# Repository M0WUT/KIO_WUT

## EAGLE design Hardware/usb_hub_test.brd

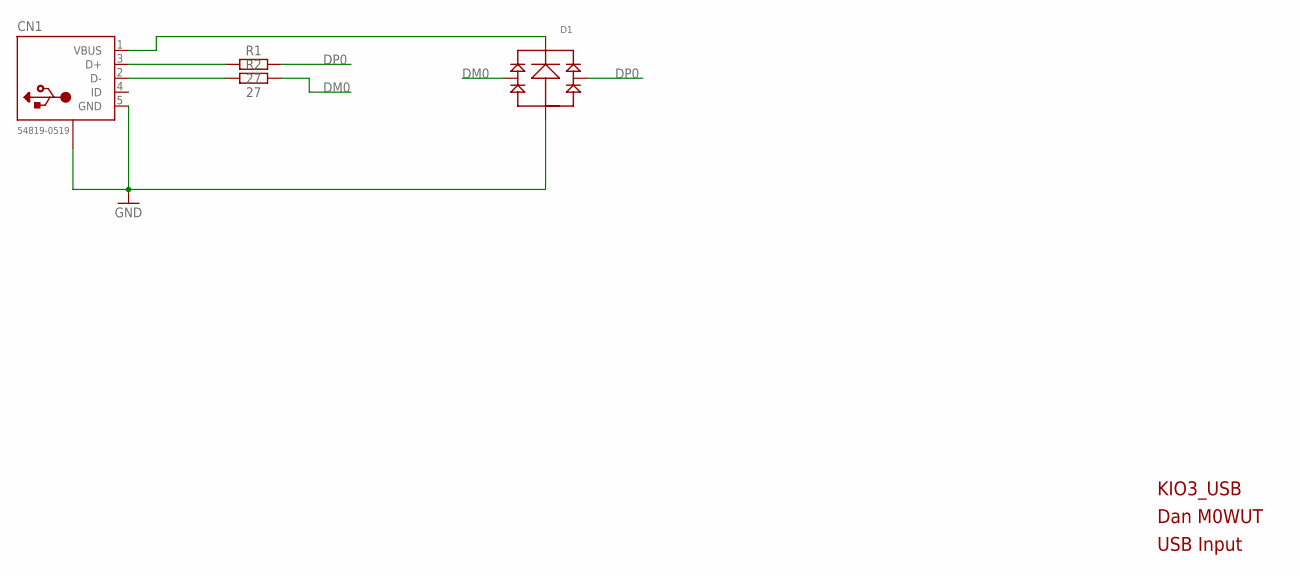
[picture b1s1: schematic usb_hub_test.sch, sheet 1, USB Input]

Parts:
CN1: 54819-0519; CONN_AMP_MUSB_K152
D1: D_ST_USBULC6; UQFN6
R1, R2: 27; R0402

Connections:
D+_P: CN1.3 (D+), R1.1
DM0: D1.1 (LEFT), D1.6 (LEFT), R2.2; also elsewhere on the board
DP0: D1.3 (RIGHT), D1.4 (RIGHT), R1.2; also elsewhere on the board
GND: CN1.5 (GND), CN1.GND1 (SHIELD), CN1.GND2 (SHIELD), D1.2 (GND); also elsewhere on the board
unnamed: CN1.2 (D-), R2.1
VBUS: CN1.1 (VBUS), D1.5 (V+)

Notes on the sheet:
KIO3_USB
Dan M0WUT
USB Input

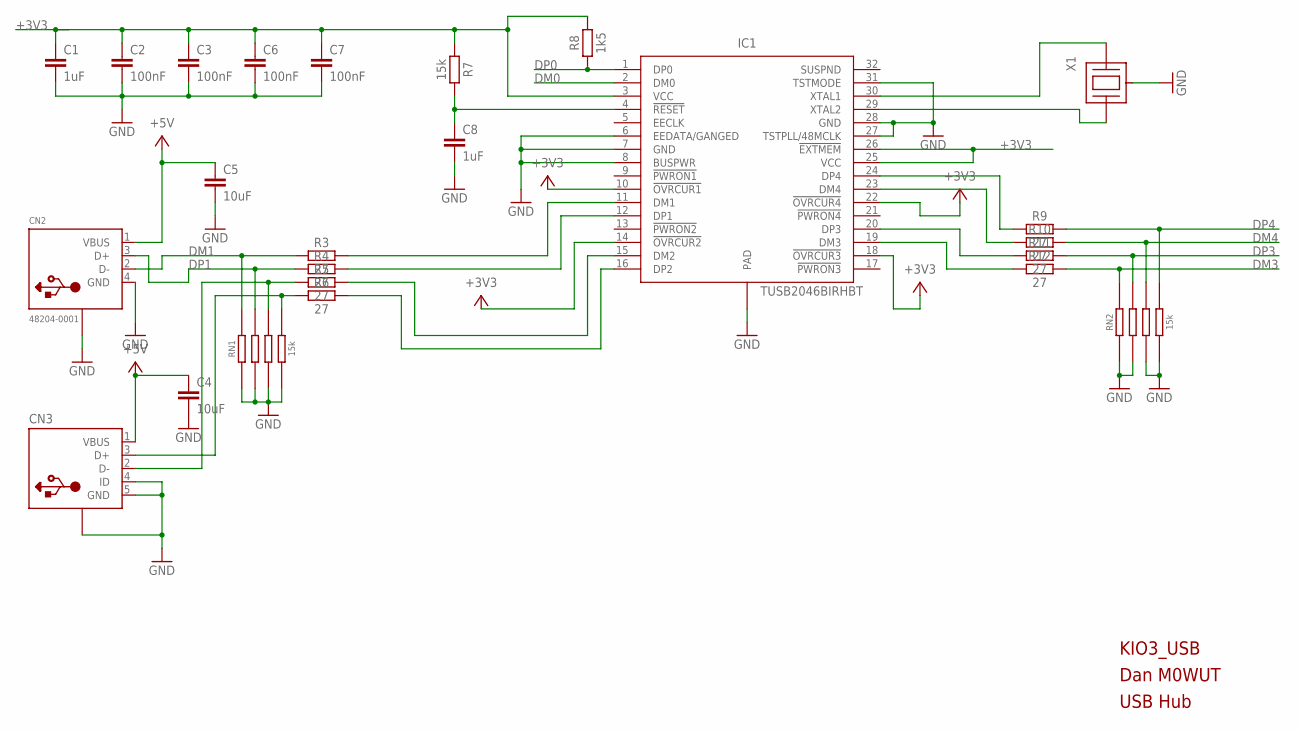
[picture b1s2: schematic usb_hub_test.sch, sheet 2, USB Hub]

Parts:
C1, C8: 1uF; C0402
C2, C3, C6, C7: 100nF; C0402
C4, C5: 10uF; C0805
CN2: 48204-0001; CONN_USB_MOLEX_RA
CN3: USBWURTH; USB_MICROB_WURTH
IC1: TUSB2046BIRHBT; RHB_S-PQFP-N32
R3, R4, R5, R6, R9, R10, R11, R12: 27; R0402
R7: 15k; R0402
R8: 1k5; R0402
RN1, RN2: 15k; R_BOURNS_CAY16-J4
X1: XTAL_MURATA_3-PIN-RES

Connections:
+3V3: C1.1, C2.1, C3.1, C6.1, C7.1, IC1.3 (VCC), IC1.10 (!OVRCUR1), IC1.14 (!OVRCUR2), IC1.18 (!OVRCUR3), IC1.22 (!OVRCUR4), IC1.25 (VCC), IC1.26 (!EXTMEM), R7.1, R8.2; also elsewhere on the board
+5V: C4.1, C5.1, CN2.1 (VBUS), CN3.1 (VBUS); also elsewhere on the board
DM0: IC1.2 (DM0); also elsewhere on the board
DM1: CN2.2 (D-), R3.1, RN1.1A
DM2: CN3.2 (D-), R5.1, RN1.3A
DM3: R12.2, RN2.1A; also elsewhere on the board
DM4: R10.2, RN2.3A; also elsewhere on the board
DP0: IC1.1 (DP0), R8.1; also elsewhere on the board
DP1: CN2.3 (D+), R4.1, RN1.2A
DP2: CN3.3 (D+), R6.1, RN1.4A
DP3: R11.2, RN2.2A; also elsewhere on the board
DP4: R9.2, RN2.4A; also elsewhere on the board
GND: C1.2, C2.2, C3.2, C4.2, C5.2, C6.2, C7.2, C8.2, CN2.4 (GND), CN2.P$2 (SHIELD), CN2.P$3 (SHIELD), CN2.P$4 (SHIELD), CN2.P$5 (SHIELD), CN3.4 (ID), CN3.5 (GND), CN3.GND1 (SHIELD), CN3.GND2 (SHIELD), CN3.GND3 (SHIELD), CN3.GND4 (SHIELD), IC1.6 (EEDATA/GANGED), IC1.7 (GND), IC1.8 (BUSPWR), IC1.27 (TSTPLL/48MCLK), IC1.28 (GND), IC1.31 (TSTMODE), IC1.EXP (PAD), RN1.1, RN1.2, RN1.3, RN1.4, RN2.1, RN2.2, RN2.3, RN2.4, X1.GND (CAN); also elsewhere on the board
unnamed: IC1.23 (DM4), R10.1
unnamed: IC1.24 (DP4), R9.1
unnamed: IC1.30 (XTAL1), X1.1 (XTAL1)
unnamed: C8.1, IC1.4 (!RESET), R7.2
unnamed: IC1.29 (XTAL2), X1.2 (XTAL2)
unnamed: IC1.15 (DM2), R5.2
unnamed: IC1.11 (DM1), R3.2
unnamed: IC1.12 (DP1), R4.2
unnamed: IC1.16 (DP2), R6.2
unnamed: IC1.20 (DP3), R11.1
unnamed: IC1.19 (DM3), R12.1

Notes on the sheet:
KIO3_USB
Dan M0WUT
USB Hub

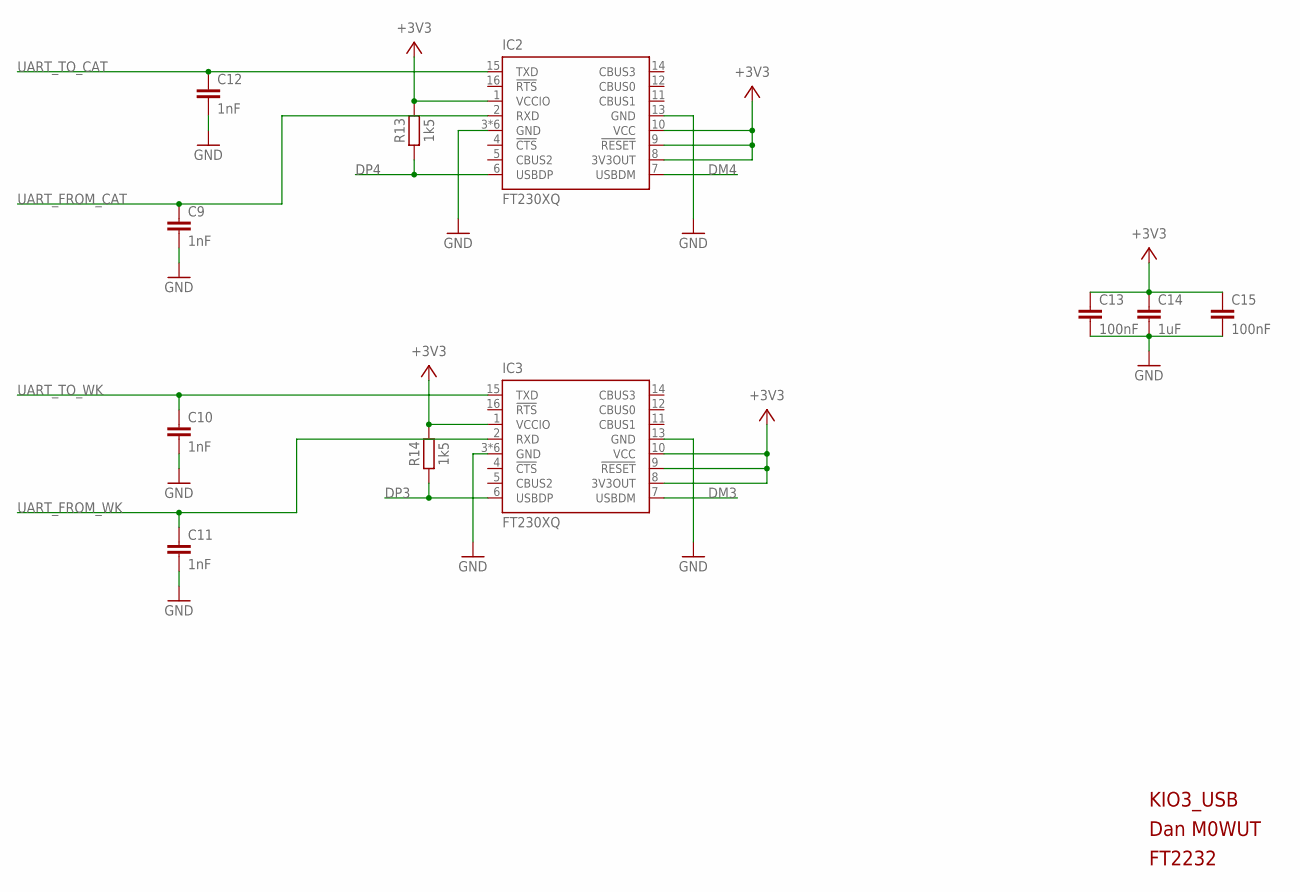
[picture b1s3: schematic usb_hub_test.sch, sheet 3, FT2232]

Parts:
C9, C10, C11, C12: 1nF; C0402
C13, C15: 100nF; C0402
C14: 1uF; C0402
IC2, IC3: FT230XQ; QFN16
R13, R14: 1k5; R0402

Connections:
+3V3: C13.1, C14.1, C15.1, IC2.1 (VCCIO), IC2.8 (3V3OUT), IC2.9 (!RESET), IC2.10 (VCC), IC3.1 (VCCIO), IC3.8 (3V3OUT), IC3.9 (!RESET), IC3.10 (VCC), R13.2, R14.2; also elsewhere on the board
DM3: IC3.7 (USBDM); also elsewhere on the board
DM4: IC2.7 (USBDM); also elsewhere on the board
DP3: IC3.6 (USBDP), R14.1; also elsewhere on the board
DP4: IC2.6 (USBDP), R13.1; also elsewhere on the board
GND: C9.2, C10.2, C11.2, C12.2, C13.2, C14.2, C15.2, IC2.3 (GND), IC2.13 (GND), IC2.P$1 (GND), IC2.P$2 (GND), IC2.P$3 (GND), IC2.P$4 (GND), IC2.TAB (GND), IC3.3 (GND), IC3.13 (GND), IC3.P$1 (GND), IC3.P$2 (GND), IC3.P$3 (GND), IC3.P$4 (GND), IC3.TAB (GND); also elsewhere on the board
UART_FROM_CAT: C9.1, IC2.2 (RXD); also elsewhere on the board
UART_FROM_WK: C11.1, IC3.2 (RXD); also elsewhere on the board
UART_TO_CAT: C12.1, IC2.15 (TXD); also elsewhere on the board
UART_TO_WK: C10.1, IC3.15 (TXD); also elsewhere on the board

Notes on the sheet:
KIO3_USB
Dan M0WUT
FT2232

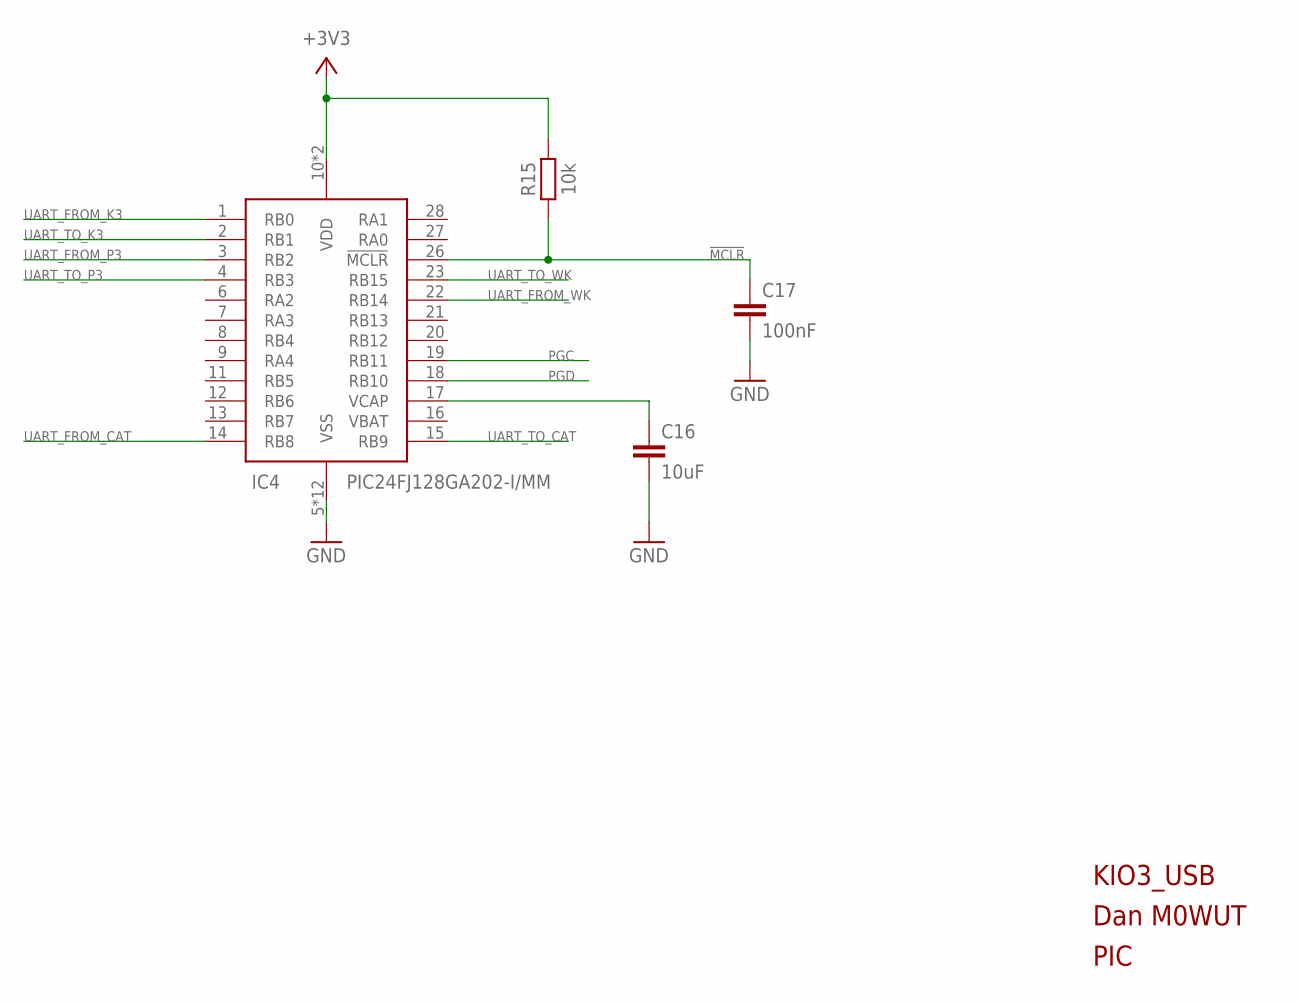
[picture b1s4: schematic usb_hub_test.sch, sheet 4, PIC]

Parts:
C16: 10uF; C0805
C17: 100nF; C0402
IC4: PIC24FJ128GA202-I/MM; QFN28-ML_6X6MM
R15: 10k; R0402

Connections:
!MCLR: C17.1, IC4.26 (!MCLR), R15.1
+3V3: IC4.10 (VDD), IC4.25 (VDD), R15.2; also elsewhere on the board
GND: C16.2, C17.2, IC4.5 (VSS), IC4.24 (VSS), IC4.EXP (VSS), IC4.P$1 (VSS), IC4.P$2 (VSS), IC4.P$3 (VSS), IC4.P$4 (VSS), IC4.P$5 (VSS), IC4.P$6 (VSS), IC4.P$7 (VSS), IC4.P$9 (VSS), IC4.P$10 (VSS); also elsewhere on the board
unnamed: C16.1, IC4.17 (VCAP)
PGC: IC4.19 (RB11)
PGD: IC4.18 (RB10)
UART_FROM_CAT: IC4.14 (RB8); also elsewhere on the board
UART_FROM_K3: IC4.1 (RB0); also elsewhere on the board
UART_FROM_P3: IC4.3 (RB2); also elsewhere on the board
UART_FROM_WK: IC4.22 (RB14); also elsewhere on the board
UART_TO_CAT: IC4.15 (RB9); also elsewhere on the board
UART_TO_K3: IC4.2 (RB1); also elsewhere on the board
UART_TO_P3: IC4.4 (RB3); also elsewhere on the board
UART_TO_WK: IC4.23 (RB15); also elsewhere on the board

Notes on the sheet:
KIO3_USB
Dan M0WUT
PIC

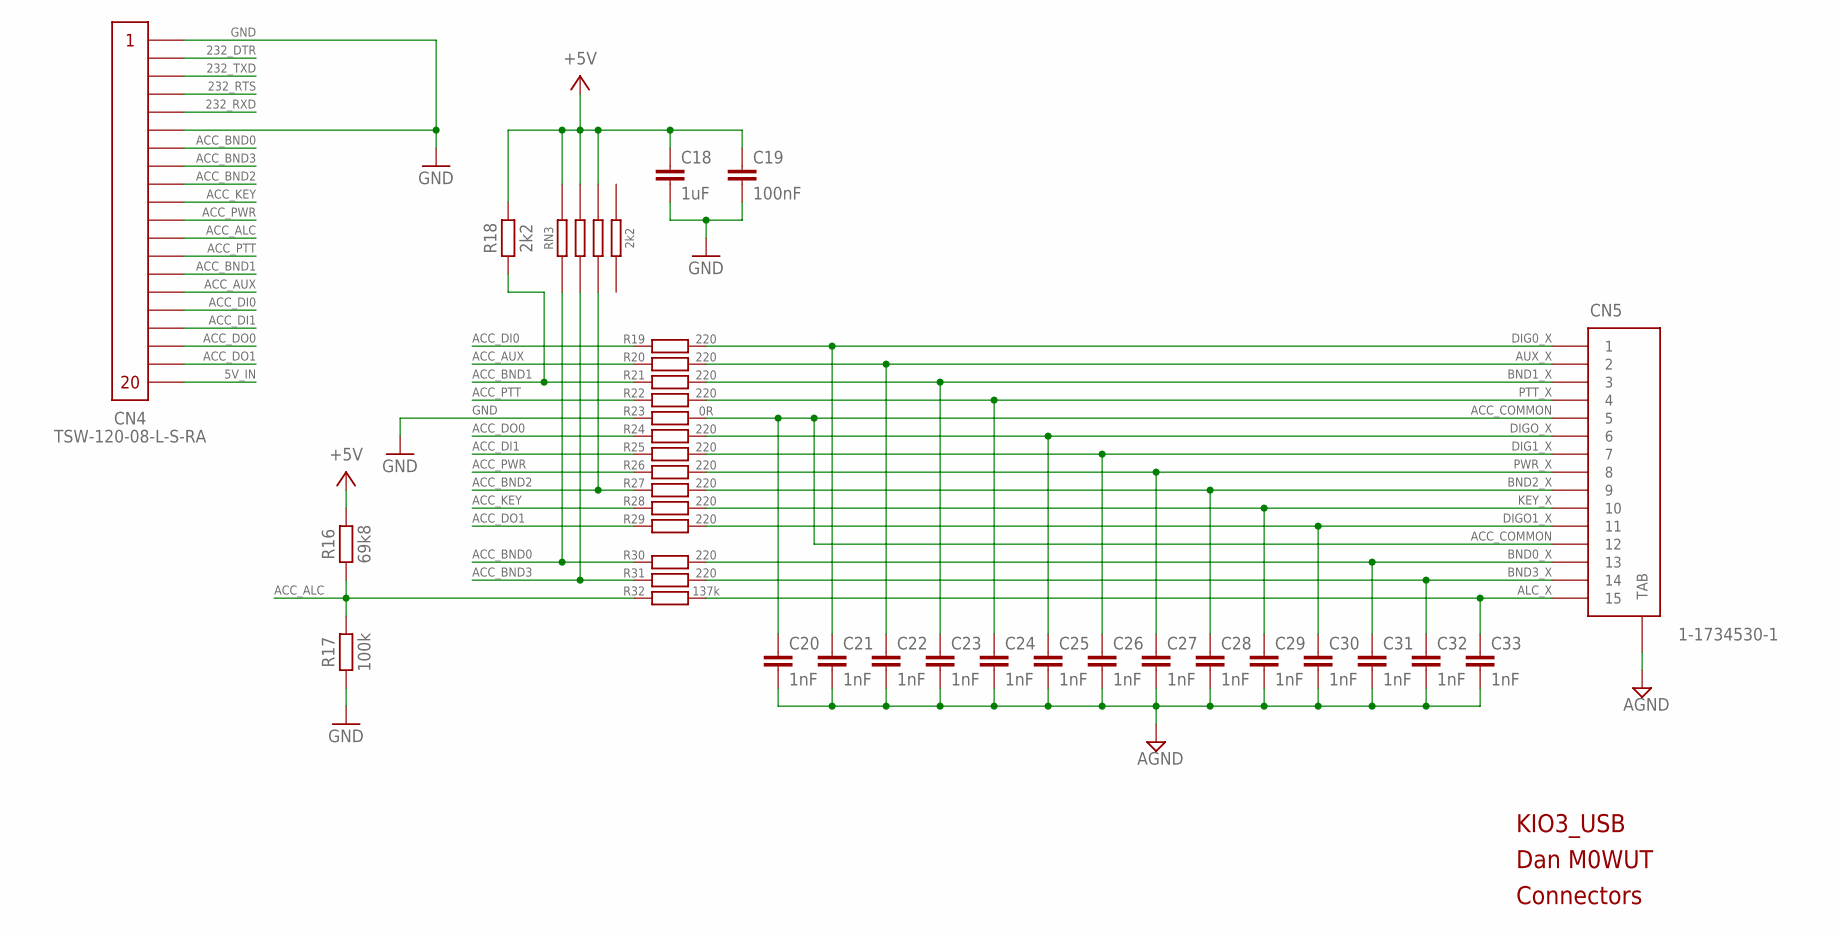
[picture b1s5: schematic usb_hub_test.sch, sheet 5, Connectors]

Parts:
C18: 1uF; C0402
C19: 100nF; C0402
C20, C21, C22, C23, C24, C25, C26, C27, C28, C29, C30, C31, C32, C33: 1nF; C0402
CN4: TSW-120-08-L-S-RA; CONN_0.1_1X20
CN5: 1-1734530-1; CONN_TE_DE-HD15
R16: 69k8; R0402
R17: 100k; R0402
R18: 2k2; R0402
R19, R20, R21, R22, R24, R25, R26, R27, R28, R29, R30, R31: 220; R0402
R23: 0R; R0402
R32: 137k; R0402
RN3: 2k2; R_BOURNS_CAY16-J4

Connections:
5V_IN: CN4.P$20; also elsewhere on the board
232_DTR: CN4.P$2
232_RTS: CN4.P$4
232_RXD: CN4.P$5; also elsewhere on the board
232_TXD: CN4.P$3; also elsewhere on the board
+5V: C18.1, C19.1, R16.2, R18.2, RN3.1, RN3.2, RN3.3; also elsewhere on the board
ACC_ALC: CN4.P$12, R16.1, R17.2, R32.1
ACC_AUX: CN4.P$15, R20.1
ACC_BND0: CN4.P$7, R30.1, RN3.1A
ACC_BND1: CN4.P$14, R18.1, R21.1
ACC_BND2: CN4.P$9, R27.1, RN3.3A
ACC_BND3: CN4.P$8, R31.1, RN3.2A
ACC_COMMON: C20.1, CN5.5, CN5.12, R23.2
ACC_DI0: CN4.P$16, R19.1
ACC_DI1: CN4.P$17, R25.1
ACC_DO0: CN4.P$18, R24.1
ACC_DO1: CN4.P$19, R29.1
ACC_KEY: CN4.P$10, R28.1
ACC_PTT: CN4.P$13, R22.1
ACC_PWR: CN4.P$11, R26.1
AGND: C20.2, C21.2, C22.2, C23.2, C24.2, C25.2, C26.2, C27.2, C28.2, C29.2, C30.2, C31.2, C32.2, C33.2, CN5.16 (TAB), CN5.17 (TAB); also elsewhere on the board
ALC_X: C33.1, CN5.15, R32.2
AUX_X: C22.1, CN5.2, R20.2
BND0_X: C31.1, CN5.13, R30.2
BND1_X: C23.1, CN5.3, R21.2
BND2_X: C28.1, CN5.9, R27.2
BND3_X: C32.1, CN5.14, R31.2
DIG0_X: C21.1, CN5.1, R19.2
DIG1_X: C26.1, CN5.7, R25.2
DIGO1_X: C30.1, CN5.11, R29.2
DIGO_X: C25.1, CN5.6, R24.2
GND: C18.2, C19.2, CN4.P$1, CN4.P$6, R17.1, R23.1; also elsewhere on the board
KEY_X: C29.1, CN5.10, R28.2
PTT_X: C24.1, CN5.4, R22.2
PWR_X: C27.1, CN5.8, R26.2

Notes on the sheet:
KIO3_USB
Dan M0WUT
Connectors

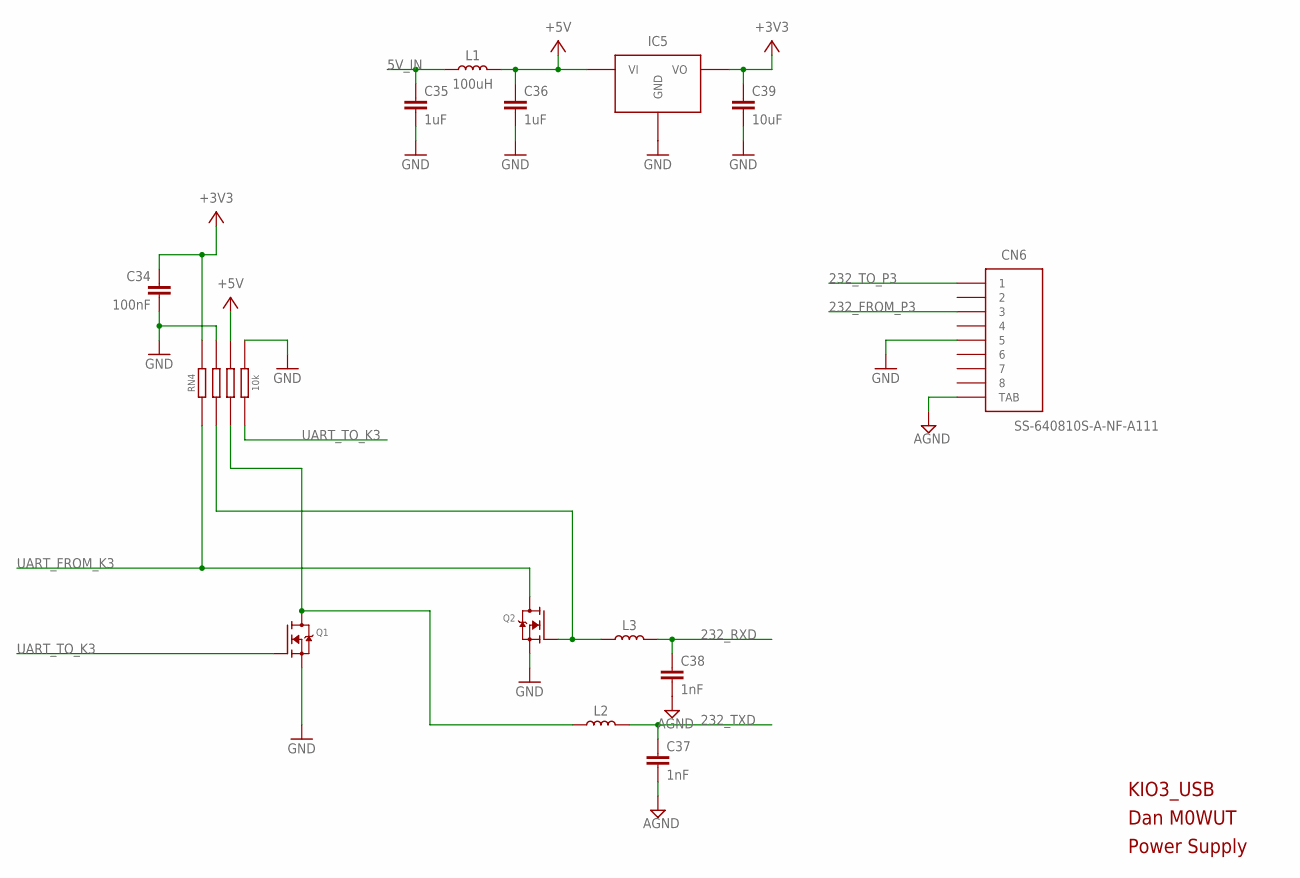
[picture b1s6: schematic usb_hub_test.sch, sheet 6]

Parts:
C34: 100nF; C0402
C35, C36: 1uF; C0402
C37, C38: 1nF; C0402
C39: 10uF; C0805
CN6: SS-640810S-A-NF-A111; CONN_STEWART_RJ45_1
IC5: MCP1700; SOT23
L1: 100uH; R0805
L2, L3: INDUCTOR; R0805
Q1, Q2: MOSFET-NREFLOW; SOT23
RN4: 10k; R_BOURNS_CAY16-J4

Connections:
5V_IN: C35.1, L1.1; also elsewhere on the board
232_FROM_P3: CN6.3; also elsewhere on the board
232_RXD: C38.1, L3.2; also elsewhere on the board
232_TO_P3: CN6.1; also elsewhere on the board
232_TXD: C37.1, L2.2; also elsewhere on the board
+3V3: C34.1, C39.1, IC5.BOTTOM_RIGHT (VO), RN4.1A; also elsewhere on the board
+5V: C36.1, IC5.TOP (VI), L1.2, RN4.3A; also elsewhere on the board
AGND: C37.2, C38.2, CN6.TAB, CN6.TAB1 (TAB); also elsewhere on the board
ASDF: L2.1, Q1.3 (D), RN4.3
GND: C34.2, C35.2, C36.2, C39.2, CN6.5, IC5.BOTTOM_LEFT (GND), Q1.2 (S), Q2.2 (S), RN4.2A, RN4.4A; also elsewhere on the board
SADF: L3.1, Q2.1 (G), RN4.2
UART_FROM_K3: Q2.3 (D), RN4.1; also elsewhere on the board
UART_TO_K3: Q1.1 (G), RN4.4; also elsewhere on the board

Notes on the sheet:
KIO3_USB
Dan M0WUT
Power Supply

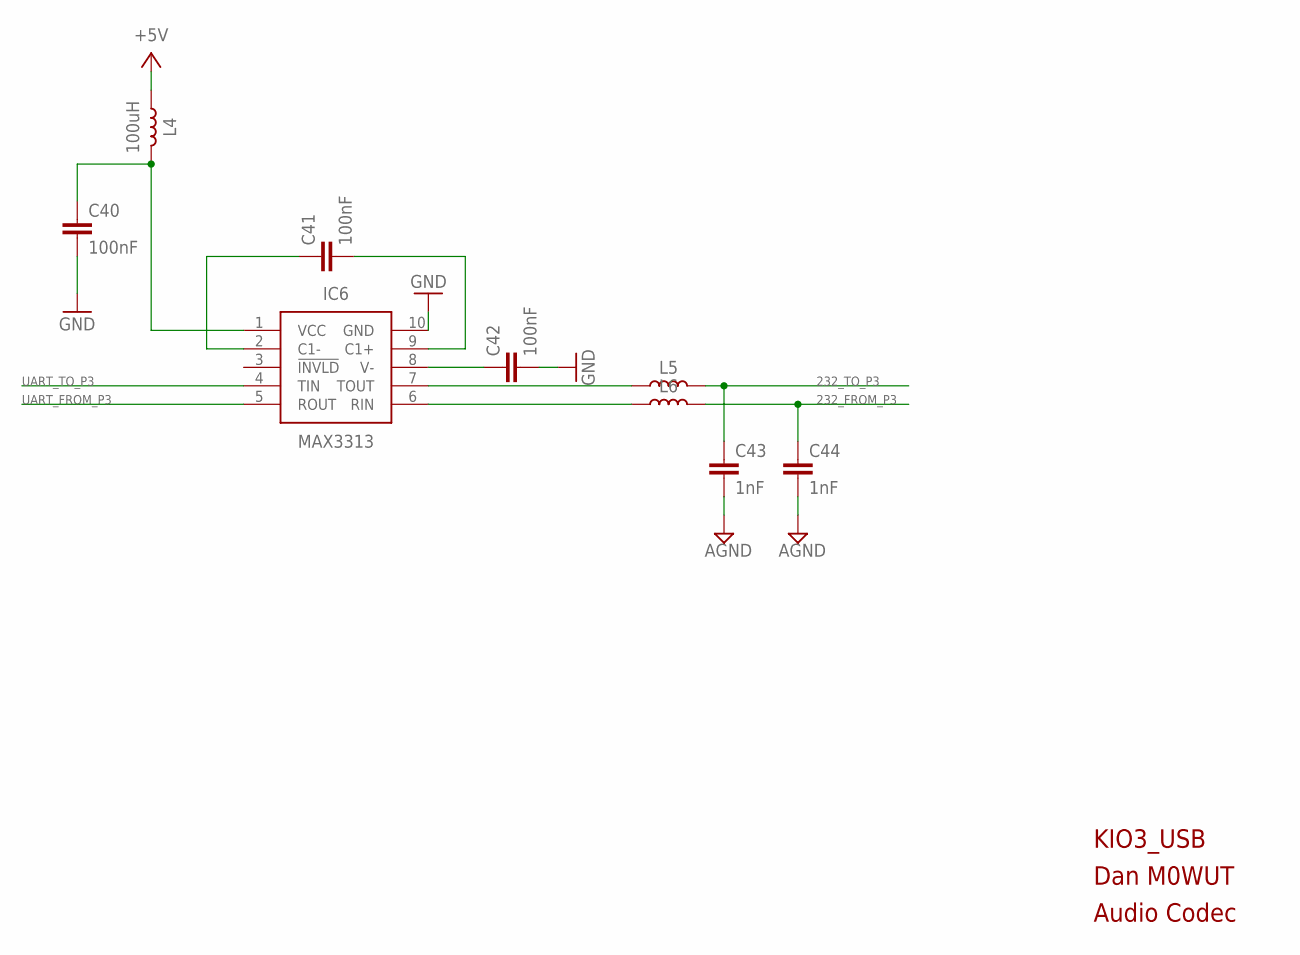
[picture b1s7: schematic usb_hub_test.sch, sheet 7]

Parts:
C40, C41, C42: 100nF; C0402
C43, C44: 1nF; C0402
IC6: IC_MAX3313; IC_UMAX10
L4: 100uH; R0805
L5, L6: INDUCTOR; R0805

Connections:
232_FROM_P3: C44.1, L6.2; also elsewhere on the board
232_TO_P3: C43.1, L5.2; also elsewhere on the board
+5V: L4.1; also elsewhere on the board
AGND: C43.2, C44.2; also elsewhere on the board
GND: C40.2, C42.2, IC6.10 (GND); also elsewhere on the board
unnamed: C40.1, IC6.1 (VCC), L4.2
unnamed: C41.1, IC6.2 (C1-)
unnamed: C41.2, IC6.9 (C1+)
unnamed: C42.1, IC6.8 (V-)
UART_FROM_P3: IC6.5 (ROUT); also elsewhere on the board
UART_TO_P3: IC6.4 (TIN); also elsewhere on the board
WTRE: IC6.7 (TOUT), L5.1
Y5W4: IC6.6 (RIN), L6.1

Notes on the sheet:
KIO3_USB
Dan M0WUT
Audio Codec

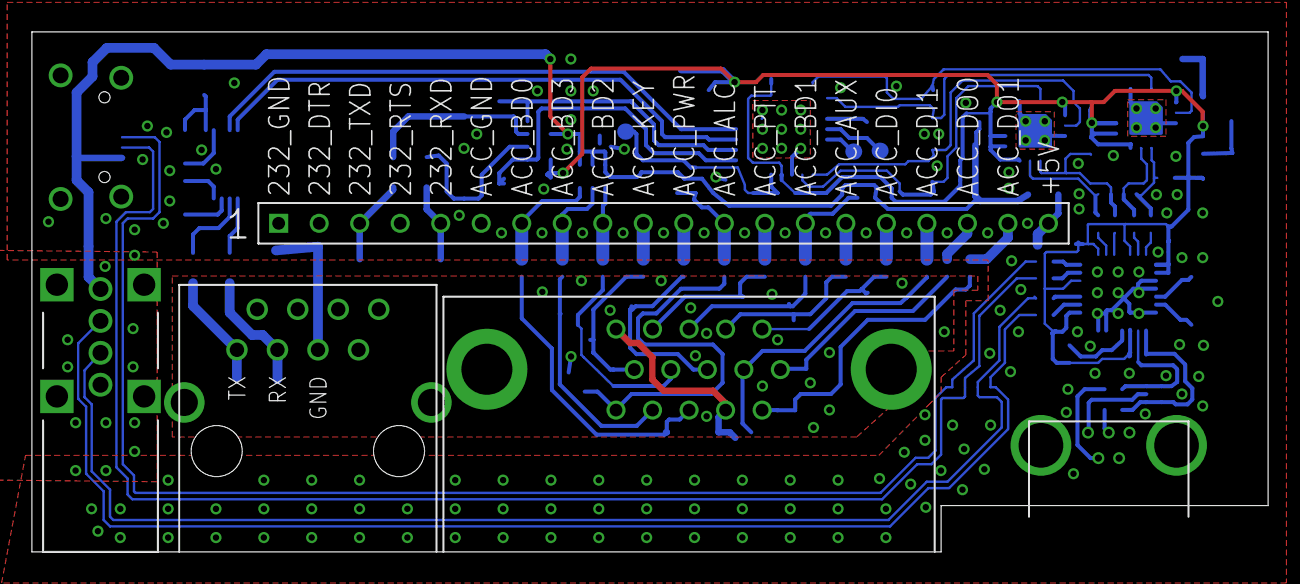
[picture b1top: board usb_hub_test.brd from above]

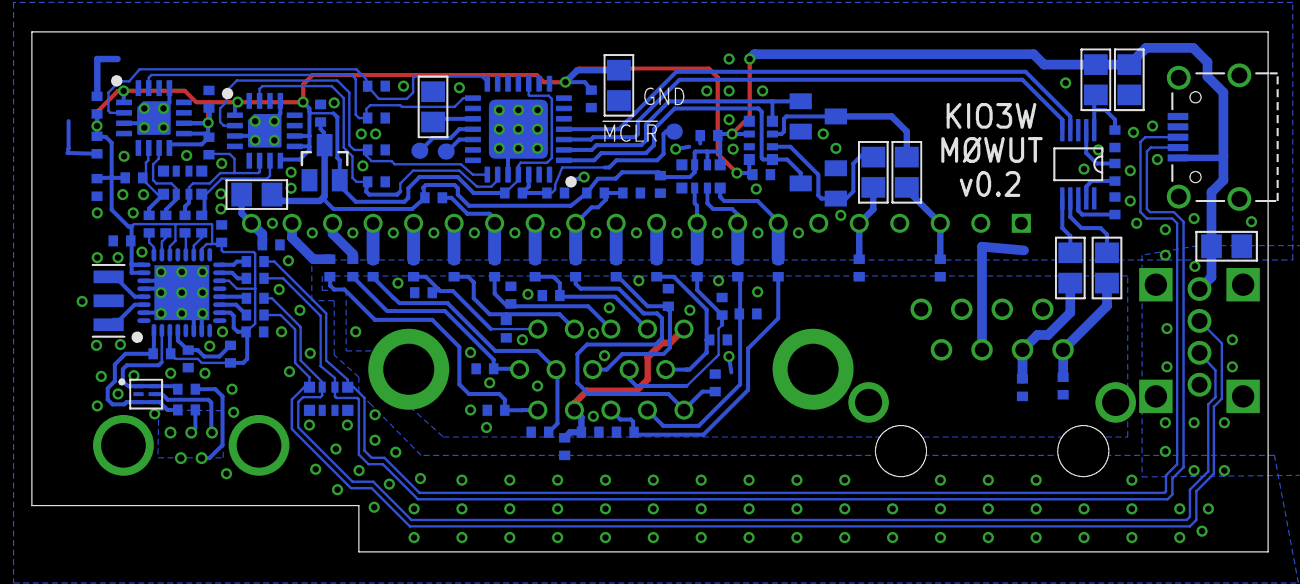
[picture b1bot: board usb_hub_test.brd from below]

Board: 2 copper layers, 77.5 x 32.6 mm, 102 parts (97 on the bottom side), 78 nets.

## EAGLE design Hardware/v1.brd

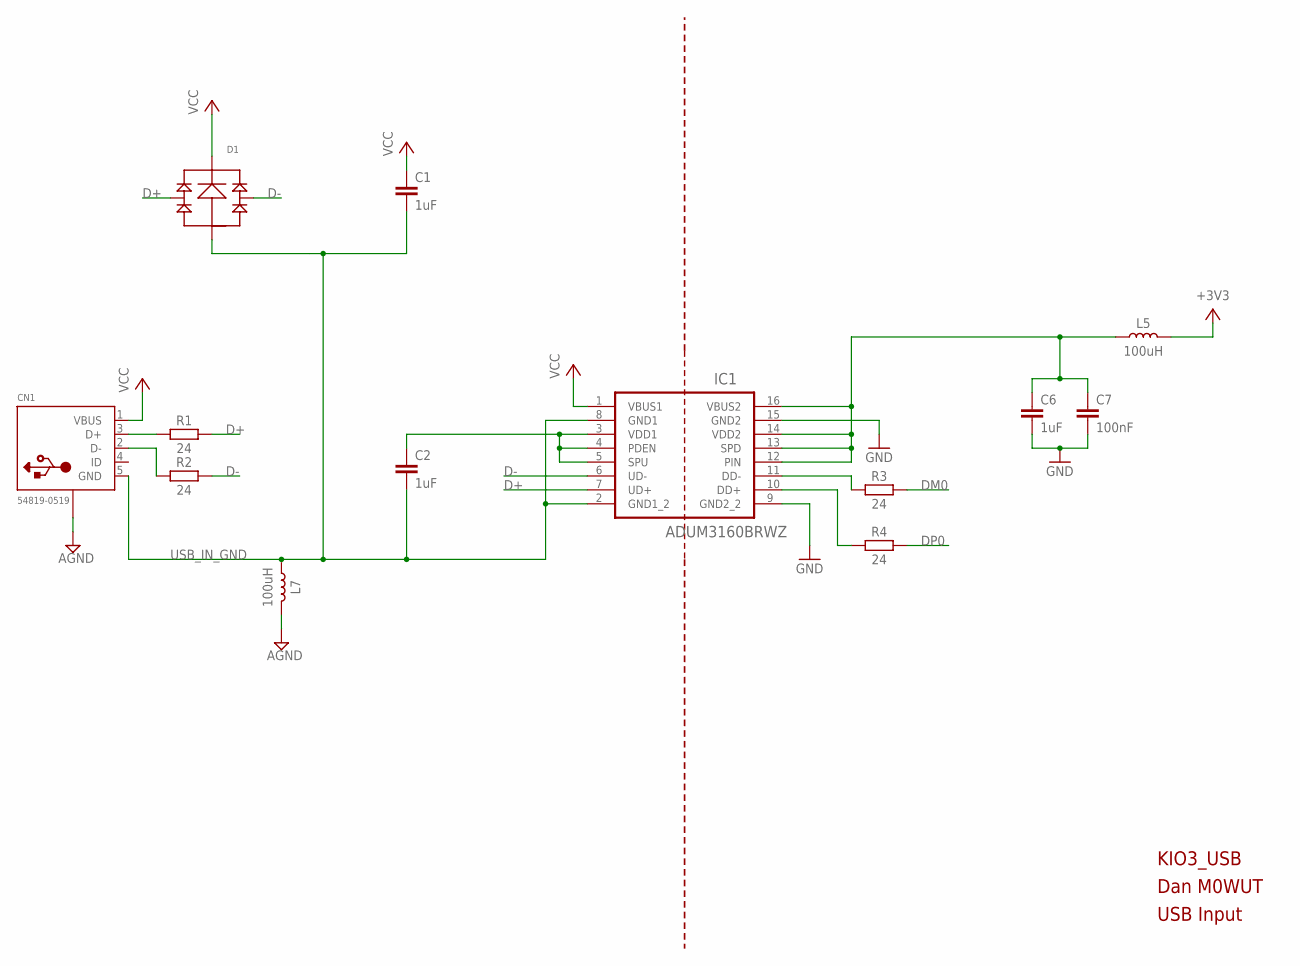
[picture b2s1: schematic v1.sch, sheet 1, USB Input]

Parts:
C1, C2, C6: 1uF; C0402
C7: 100nF; C0402
CN1: 54819-0519; CONN_USB_MOLEX_MINI
D1: D_ST_USBULC6; UQFN6
IC1: ADUM3160BRWZ; SOIC127P1032X265-16N
L5, L7: 100uH; R0805
R1, R2, R3, R4: 24; R0402

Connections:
+3V3: L5.2; also elsewhere on the board
AGND: CN1.TAB (SHIELD), CN1.TAB1 (SHIELD), L7.2; also elsewhere on the board
D+: D1.1 (LEFT), D1.6 (LEFT), IC1.7 (UD+), R1.2
D-: D1.3 (RIGHT), D1.4 (RIGHT), IC1.6 (UD-), R2.2
DM0: R3.2; also elsewhere on the board
DP0: R4.2; also elsewhere on the board
GND: C6.2, C7.2, IC1.9 (GND2_2), IC1.15 (GND2); also elsewhere on the board
unnamed: CN1.3 (D+), R1.1
unnamed: CN1.2 (D-), R2.1
unnamed: C2.1, IC1.3 (VDD1), IC1.4 (PDEN), IC1.5 (SPU)
unnamed: IC1.11 (DD-), R3.1
unnamed: IC1.10 (DD+), R4.1
unnamed: C6.1, C7.1, IC1.12 (PIN), IC1.13 (SPD), IC1.14 (VDD2), IC1.16 (VBUS2), L5.1
USB_IN_GND: C1.2, C2.2, CN1.5 (GND), D1.2 (GND), IC1.2 (GND1_2), IC1.8 (GND1), L7.1
VCC: C1.1, CN1.1 (VBUS), D1.5 (V+), IC1.1 (VBUS1)

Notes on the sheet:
KIO3_USB
Dan M0WUT
USB Input

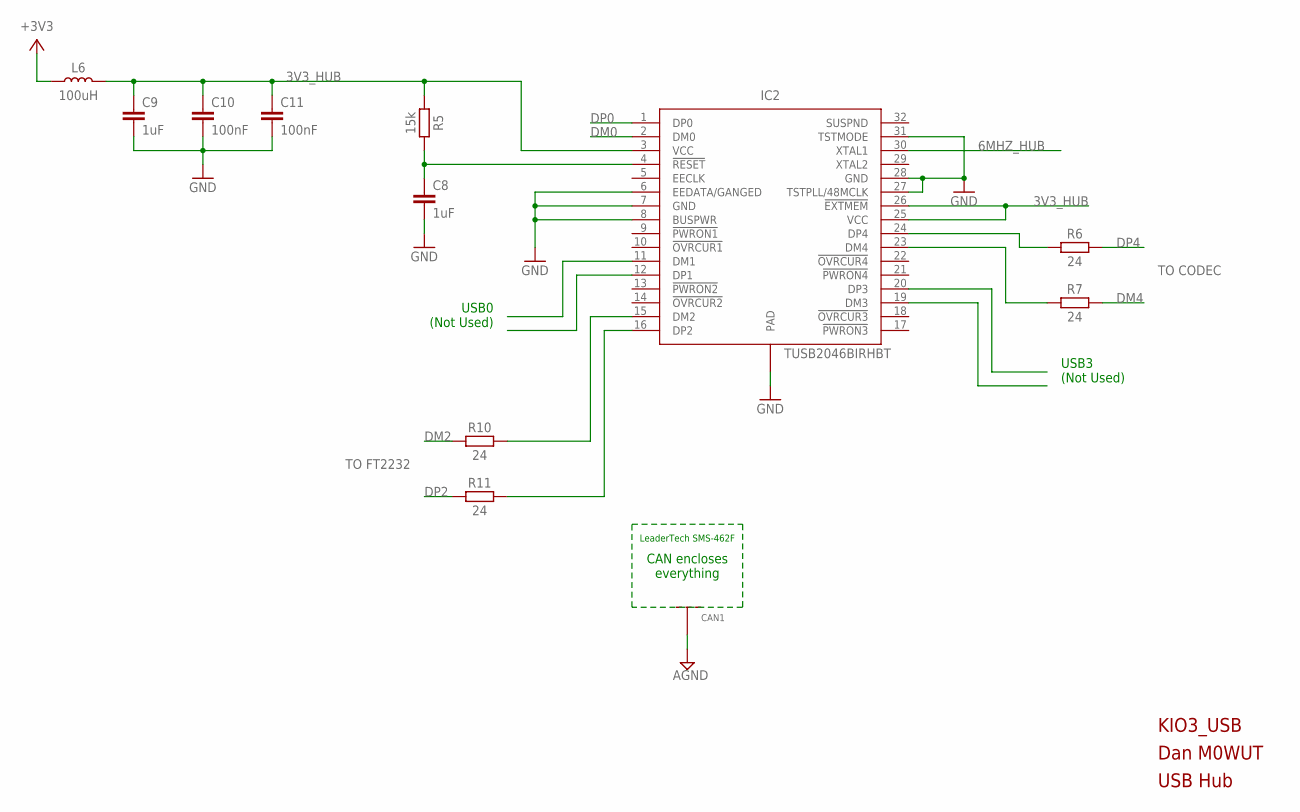
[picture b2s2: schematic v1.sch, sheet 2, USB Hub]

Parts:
C8, C9: 1uF; C0402
C10, C11: 100nF; C0402
CAN1: SHIELDING_CAN; CAN_LEADER_SMS462
IC2: TUSB2046BIRHBT; RHB_S-PQFP-N32
L6: 100uH; R0805
R5: 15k; R0402
R6, R7, R10, R11: 24; R0402

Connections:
3V3_HUB: C9.1, C10.1, C11.1, IC2.3 (VCC), IC2.25 (VCC), IC2.26 (!EXTMEM), L6.2, R5.1
6MHZ_HUB: IC2.30 (XTAL1)
+3V3: L6.1; also elsewhere on the board
AGND: CAN1.P$1, CAN1.P$2, CAN1.P$3, CAN1.P$4, CAN1.P$5, CAN1.P$6, CAN1.P$7, CAN1.P$8, CAN1.P$9, CAN1.P$10, CAN1.P$11, CAN1.P$12, CAN1.P$13, CAN1.P$14, CAN1.P$15, CAN1.P$16, CAN1.P$17, CAN1.P$18, CAN1.P$19, CAN1.P$20, CAN1.P$21, CAN1.P$22, CAN1.P$23, CAN1.P$24, CAN1.P$25, CAN1.P$26, CAN1.P$27, CAN1.P$28, CAN1.P$29, CAN1.P$30, CAN1.P$31, CAN1.P$32, CAN1.P$33, CAN1.P$34, CAN1.P$35, CAN1.P$36, CAN1.P$37, CAN1.P$38, CAN1.P$39, CAN1.P$40, CAN1.P$41, CAN1.P$42, CAN1.P$43, CAN1.P$44, CAN1.P$45, CAN1.P$46, CAN1.P$47, CAN1.P$48, CAN1.P$49, CAN1.P$50, CAN1.P$51, CAN1.P$52, CAN1.P$53, CAN1.P$54, CAN1.P$55, CAN1.P$56, CAN1.P$57, CAN1.P$58, CAN1.P$59, CAN1.P$60, CAN1.P$61, CAN1.P$62, CAN1.P$63, CAN1.P$64, CAN1.P$65, CAN1.P$66, CAN1.P$67, CAN1.P$68; also elsewhere on the board
DM0: IC2.2 (DM0); also elsewhere on the board
DM2: R10.1; also elsewhere on the board
DM4: R7.2
DP0: IC2.1 (DP0); also elsewhere on the board
DP2: R11.1; also elsewhere on the board
DP4: R6.2
GND: C8.2, C9.2, C10.2, C11.2, IC2.6 (EEDATA/GANGED), IC2.7 (GND), IC2.8 (BUSPWR), IC2.27 (TSTPLL/48MCLK), IC2.28 (GND), IC2.31 (TSTMODE), IC2.EXP (PAD); also elsewhere on the board
unnamed: C8.1, IC2.4 (!RESET), R5.2
unnamed: IC2.15 (DM2), R10.2
unnamed: IC2.16 (DP2), R11.2
USB4_N: IC2.23 (DM4), R7.1
USB4_P: IC2.24 (DP4), R6.1

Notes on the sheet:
KIO3_USB
Dan M0WUT
USB Hub
TO FT2232
TO CODEC
USB0 (Not Used)
USB3 (Not Used)
CAN encloses everything
LeaderTech SMS-462F

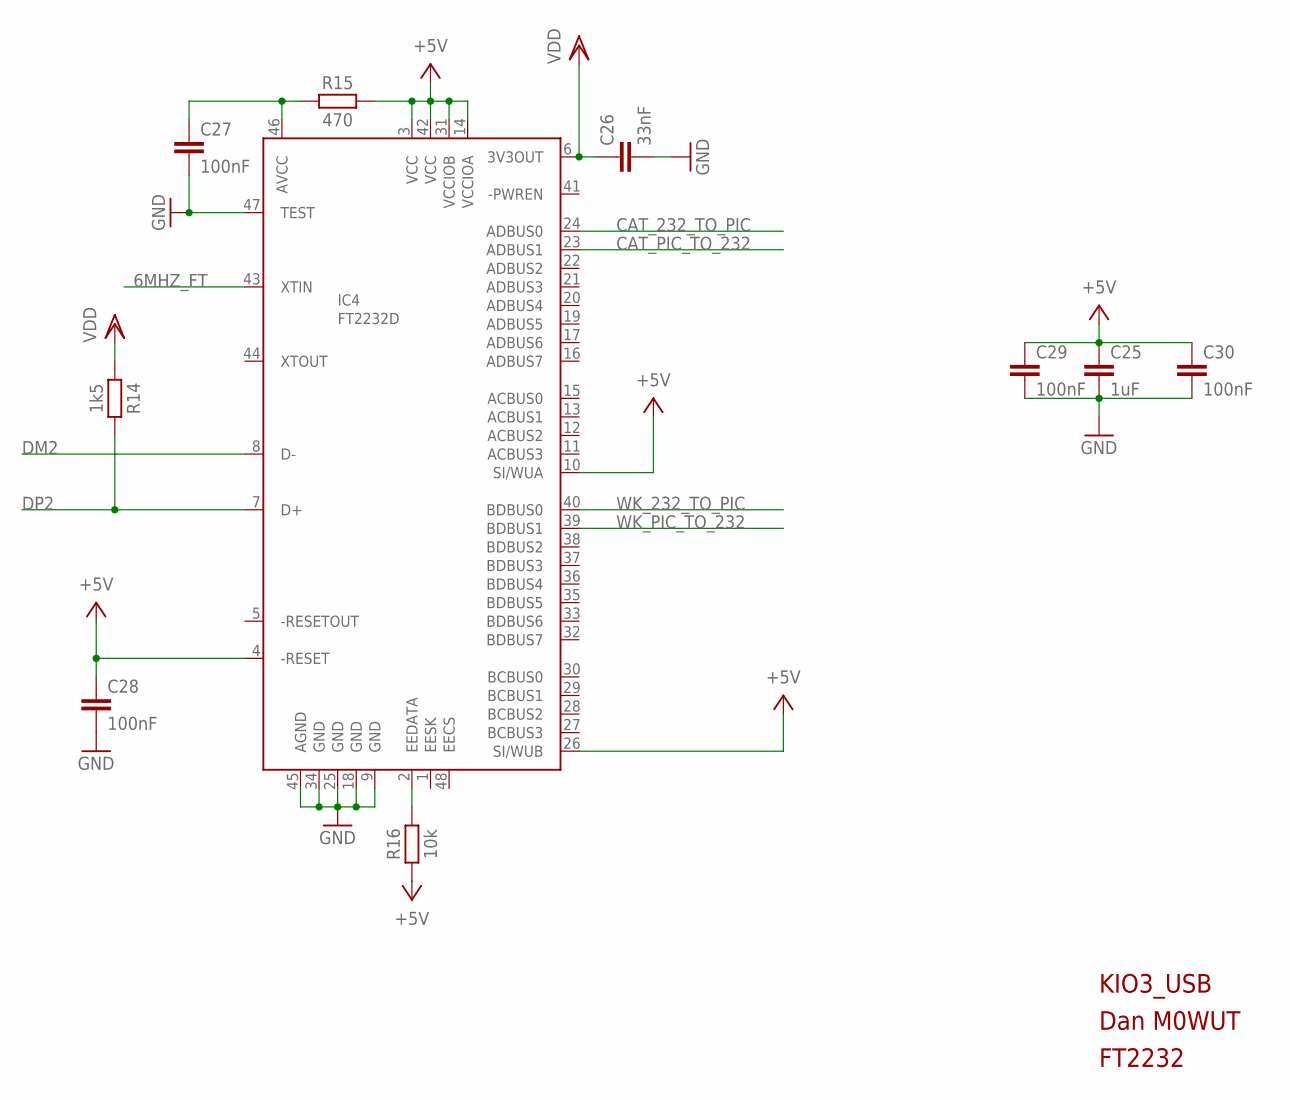
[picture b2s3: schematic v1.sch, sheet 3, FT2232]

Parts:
C25: 1uF; C0402
C26: 33nF; C0402
C27, C28, C29, C30: 100nF; C0402
IC4: FT2232D; QFP48-7X7
R14: 1k5; R0402
R15: 470; R0402
R16: 10k; R0402

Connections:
6MHZ_FT: IC4.43 (XTIN)
+5V: C25.1, C28.1, C29.1, C30.1, IC4.3 (VCC), IC4.4 (-RESET), IC4.10 (SI/WUA), IC4.14 (VCCIOA), IC4.26 (SI/WUB), IC4.31 (VCCIOB), IC4.42 (VCC), R15.2, R16.1; also elsewhere on the board
CAT_232_TO_PIC: IC4.24 (ADBUS0)
CAT_PIC_TO_232: IC4.23 (ADBUS1)
DM2: IC4.8 (D-); also elsewhere on the board
DP2: IC4.7 (D+), R14.2; also elsewhere on the board
GND: C25.2, C26.2, C27.2, C28.2, C29.2, C30.2, IC4.9 (GND), IC4.18 (GND), IC4.25 (GND), IC4.34 (GND), IC4.45 (AGND), IC4.47 (TEST); also elsewhere on the board
unnamed: C27.1, IC4.46 (AVCC), R15.1
unnamed: IC4.2 (EEDATA), R16.2
VDD: C26.1, IC4.6 (3V3OUT), R14.1
WK_232_TO_PIC: IC4.40 (BDBUS0)
WK_PIC_TO_232: IC4.39 (BDBUS1)

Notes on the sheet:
KIO3_USB
Dan M0WUT
FT2232

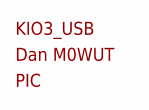
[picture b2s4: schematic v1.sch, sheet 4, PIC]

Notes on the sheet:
KIO3_USB
Dan M0WUT
PIC
